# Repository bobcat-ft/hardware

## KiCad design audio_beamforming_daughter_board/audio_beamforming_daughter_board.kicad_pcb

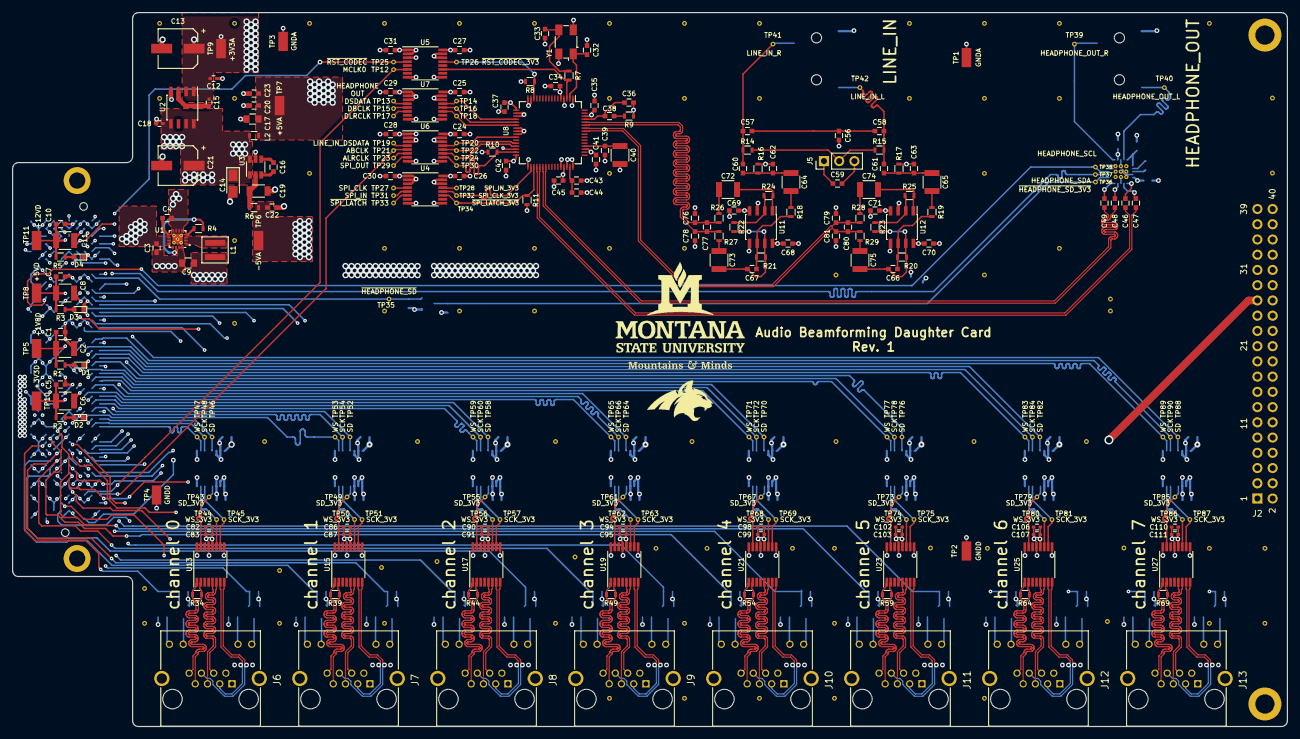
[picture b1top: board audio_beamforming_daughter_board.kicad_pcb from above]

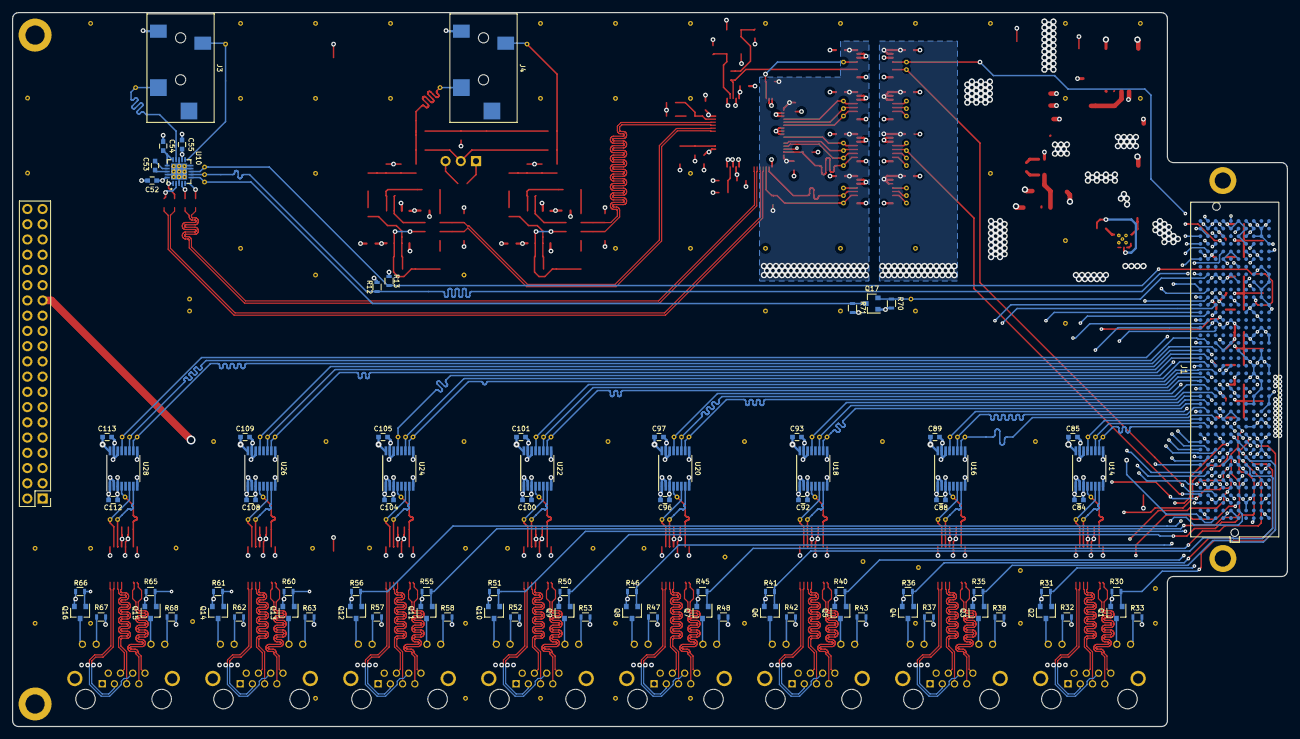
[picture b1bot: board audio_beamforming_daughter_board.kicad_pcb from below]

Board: 6 copper layers, 212.5 x 119.0 mm, 412 parts (86 on the bottom side), 266 nets.

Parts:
C1, C5, C7, C10, C22, C44: 10uF; C_0603
C2, C6, C8, C11: 100uF; C_1210
C3, C20: 10nF; C_0603
C4: 3300pF; C_0603
C9, C17: 22uF; C_0805
C12, C18, C82, C86, C90, C94, C98, C102, C106, C110: 0.1uF; C_0402
C13, C21: 47uF; CP_Elec_6.3x5.8
C14: 10uF; CP_Tantalum_Case-A_EIA-3216-18_Reflow
C15: 10nF; C_0402
C16, C23, C24, C25, C26, C27, C28, C29, C30, C31, C34, C35, C37, C39, C41, C42, C43, C45, C59, C68, C69, C70, C71, C84, C85, C88, C89, C92, C93, C96, C97, C100, C101, C104, C105, C108, C109, C112, C113: 0.1uF; C_0603
C19: 22uF; C_1206
C32, C33: 22pF; C_0603
C36: 390pF; C_0603
C38: 5600pF; C_0603
C40, C64, C65, C72, C73, C74, C75: 47uF; C_1210
C46, C47, C48, C49: 0.47uF; C_0603
C52, C53, C54, C55, C60, C61: 1.0uF; C_0603
C56, C57, C58, C76, C78, C79, C81: 1000pF; C_0603
C62, C63, C77, C80: 100pF; C_0603
C66, C67: 120pF; C_0603
C83, C87, C91, C95, C99, C103, C107, C111: 4700pF; C_0402
D1, D2, D3, D4: SML-LX0603SRW-TR; LED_0603
J1: ASP-134488-01; asp-134488-01
J2: TSW-120-07-F-D; Pin_Header_Straight_2x20_Pitch2.54mm
J3, J4: SJ-3523-SMT-TR; sj-352x-smt
J5: TSW-103-07-G-S; Pin_Header_Straight_1x03_Pitch2.54mm
J6, J7, J8, J9, J10, J11, J12, J13: 615008137421; WURTH_615008137421
L1: 2.2uH; xfl4020
L2: BLM18BA220SN1D; L_0603
Q1, Q2, Q3, Q4, Q5, Q6, Q7, Q8, Q9, Q10, Q11, Q12, Q13, Q14, Q15, Q16, Q17: NX138AKR; SOT-23
R1: 6.2; R_0603
R2: 107; R_0603
R3: 220; R_0603
R4: 100k; R_0603
R5: 680; R_0603
R6: 3.9; R_0603
R7: 49.9; R_0603
R8, R10, R11, R12, R13, R30, R31, R35, R36, R40, R41, R45, R46, R50, R51, R55, R56, R60, R61, R65, R66, R70, R71: 10k; R_0603
R9: 562; R_0603
R14, R15: 6.81k; R_0603
R16, R17: 4.99k; R_0603
R18, R19, R20, R21, R22, R23, R24, R25: 5.76k; R_0603
R26, R27, R28, R29: 237; R_0603
R32, R33, R37, R38, R42, R43, R47, R48, R52, R53, R57, R58, R62, R63, R67, R68: 330; R_0603
R34, R39, R44, R49, R54, R59, R64, R69: 100; R_0603
TP1, TP3: GNDA; Measurement_Point_SMD_1206
TP2, TP4: GNDD; Measurement_Point_SMD_1206
TP5: +1V8D; Measurement_Point_SMD_1206
TP6: -5VA; Measurement_Point_SMD_1206
TP7: +5VA; Measurement_Point_SMD_1206
TP8: +5VD; Measurement_Point_SMD_1206
TP9: +3V3A; Measurement_Point_SMD_1206
TP10: +3V3D; Measurement_Point_SMD_1206
TP11: +12VD; Measurement_Point_SMD_1206
TP12: MCLK0; Measurement_Point_Round-TH_0.4mm
TP13: HEADPHONE_OUT_DSDATA; Measurement_Point_Round-TH_0.4mm
TP14: HEADPHONE_OUT_DSDATA_3V3; Measurement_Point_Round-TH_0.4mm
TP15: DBCLK; Measurement_Point_Round-TH_0.4mm
TP16: DBCLK_3V3; Measurement_Point_Round-TH_0.4mm
TP17: DLRCLK; Measurement_Point_Round-TH_0.4mm
TP18: DLRCLK_3V3; Measurement_Point_Round-TH_0.4mm
TP19: LINE_IN_DSDATA; Measurement_Point_Round-TH_0.4mm
TP20: LINE_IN_DSDATA_3V3; Measurement_Point_Round-TH_0.4mm
TP21: ABCLK; Measurement_Point_Round-TH_0.4mm
TP22: ABCLK_3V3; Measurement_Point_Round-TH_0.4mm
TP23: ALRCLK; Measurement_Point_Round-TH_0.4mm
TP24: ALRCLK_3V3; Measurement_Point_Round-TH_0.4mm
TP25: ~RST_CODEC; Measurement_Point_Round-TH_0.4mm
TP26: ~RST_CODEC_3V3; Measurement_Point_Round-TH_0.4mm
TP27: SPI_IN; Measurement_Point_Round-TH_0.4mm
TP28: SPI_IN_3V3; Measurement_Point_Round-TH_0.4mm
TP29: SPI_OUT; Measurement_Point_Round-TH_0.4mm
TP30: SPI_OUT_3V3; Measurement_Point_Round-TH_0.4mm
TP31: SPI_CLK; Measurement_Point_Round-TH_0.4mm
TP32: SPI_CLK_3V3; Measurement_Point_Round-TH_0.4mm
TP33: ~SPI_LATCH; Measurement_Point_Round-TH_0.4mm
TP34: ~SPI_LATCH_3V3; Measurement_Point_Round-TH_0.4mm
TP35: ~HEADPHONE_SD; Measurement_Point_Round-TH_0.4mm
TP36: ~HEADPHONE_SD_3V3; Measurement_Point_Round-TH_0.4mm
TP37: HEADPHONE_SDA; Measurement_Point_Round-TH_0.4mm
TP38: HEADPHONE_SCL; Measurement_Point_Round-TH_0.4mm
TP39: HEADPHONE_OUT_R; Measurement_Point_Round-TH_0.4mm
TP40: HEADPHONE_OUT_L; Measurement_Point_Round-TH_0.4mm
TP41: LINE_IN_R; Measurement_Point_Round-TH_0.4mm
TP42: LINE_IN_L; Measurement_Point_Round-TH_0.4mm
TP43, TP49, TP55, TP61, TP67, TP73, TP79, TP85: SD_3V3; Measurement_Point_Round-TH_0.4mm
TP44, TP50, TP56, TP62, TP68, TP74, TP80, TP86: WS_3V3; Measurement_Point_Round-TH_0.4mm
TP45, TP51, TP57, TP63, TP69, TP75, TP81, TP87: SCK_3V3; Measurement_Point_Round-TH_0.4mm
TP46, TP52, TP58, TP64, TP70, TP76, TP82, TP88: SD; Measurement_Point_Round-TH_0.4mm
TP47, TP53, TP59, TP65, TP71, TP77, TP83, TP89: WS; Measurement_Point_Round-TH_0.4mm
TP48, TP54, TP60, TP66, TP72, TP78, TP84, TP90: SCK; Measurement_Point_Round-TH_0.4mm
U1: TPS62153RGTT; ti_vqfn-16
U2: ADP3303ARZ-3.3-RL7; SOIC-8_3.9x4.9mm_Pitch1.27mm
U3: LTC1983ES6-5#TRMPBF; TSOT-23-6
U4, U5, U6, U7, U14, U16, U18, U20, U22, U24, U26, U28: 74AVC4T245; TSSOP-16_4.4x5mm_Pitch0.65mm
U8: AD1939YSTZ; LQFP-64_10x10mm_Pitch0.5mm
U10: TPA6130A2; ti_pwqfn_n20
U11, U12: ADA4075-2; SOIC-8_3.9x4.9mm_Pitch1.27mm
U13, U15, U17, U19, U21, U23, U25, U27: SN65LVDS049; TSSOP-16_4.4x5mm_Pitch0.65mm
V3_1, V3_2, V4_1, V4_2, V4_4, V4_5, V4_5#2, V4_5#3, V4_5#4, V4_5#5, V4_5#6, V4_5#7, V4_5#8, V4_5#9, V4_5#10, V4_5#11, V4_5#12, V4_5#13, V4_5#14, V4_5#15, V5_1, V5_3, V6_1, V6_4, V6_9, V6_9#2, V6_9#3, V6_9#4, V7_1, V7_4, V8_1, V8_4, V9_1, V9_2, V9_3, V9_4, V9_10, V10_1, V10_2, V10_4, V10_9, V10_9#2, V10_10, V11_1, V11_2, V11_10, V12_8, V12_8#2, V12_8#3, V12_8#4, V12_8#5, V12_8#6, V12_8#7, V12_8#8, V12_9, V12_10, V13_1, V13_2, V14_1, V14_2, V14_3, V14_8, V14_10, V15_1, V15_2, V15_4, V16_8, V16_8#2, V16_8#3, V17_1, V17_8, V17_8#2, V17_9, V17_9#2, V18_2, V18_3: AUTO_VIA; VIA_MATRIX
Y1: ABM3B-12.288MHZ-10-1-U-T; Crystal_SMD_Abracon_ABM3B-4pin_5.0x3.2mm

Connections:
+1V8D: C1.1, C2.1, C28.2, C29.2, C30.2, C31.2, C85.2, C89.2, C93.2, C97.2, C101.2, C105.2, C109.2, C113.2, J1.E39, J1.F40, J1.G39, J1.H01, J1.H40, J1.J39, J1.K01, J1.K40, J2.27, Q17.1, R1.2, R70.1, TP5.1, U4.1, U4.2, U4.3, U5.1, U5.2, U6.1, U7.1, U7.2, U7.3, U14.16, U16.16, U18.16, U20.16, U22.16, U24.16, U26.16, U28.16
+3V3A: C12.1, C13.1, C15.2, C34.2, C35.2, C36.2, C41.2, C45.1, R9.1, TP9.1, U2.1, U2.2, U8.5, U8.45, U8.51, U8.62
+3V3D: C5.1, C6.1, C24.2, C25.2, C26.2, C27.2, C37.1, C42.1, C82.2, C83.2, C84.2, C86.2, C87.2, C88.2, C90.2, C91.2, C92.2, C94.2, C95.2, C96.2, C98.2, C99.2, C100.2, C102.2, C103.2, C104.2, C106.2, C107.2, C108.2, C110.2, C111.2, C112.2, J1.C39, J1.D32, J1.D36, J1.D38, J1.D40, J2.31, J6.1, J7.1, J8.1, J9.1, J10.1, J11.1, J12.1, J13.1, R2.2, R8.2, R11.2, R12.1, R13.2, R32.1, R33.1, R37.1, R38.1, R42.1, R43.1, R47.1, R48.1, R52.1, R53.1, R57.1, R58.1, R62.1, R63.1, R67.1, R68.1, R71.1, TP10.1, U4.16, U5.16, U6.16, U7.16, U8.17, U8.32, U13.12, U13.16, U14.1, U14.2, U15.12, U15.16, U16.1, U16.2, U17.12, U17.16, U18.1, U18.2, U19.12, U19.16, U20.1, U20.2, U21.12, U21.16, U22.1, U22.2, U23.12, U23.16, U24.1, U24.2, U25.12, U25.16, U26.1, U26.2, U27.12, U27.16, U28.1, U28.2
+5VA: C17.1, C20.1, C23.1, C52.2, C55.2, C59.2, C68.2, C70.1, J5.3, L2.2, TP7.1, U10.12, U10.20, U11.8, U12.8
+5VD: C7.1, C8.1, C9.1, C14.1, C18.1, C21.1, J2.35, L1.2, L2.1, R3.2, R4.1, TP8.1, U1.14, U2.5, U2.7, U2.8, U3.1, U3.6
+12VD: C3.1, C10.1, C11.1, J1.C35, J1.C37, J2.39, R5.2, TP11.1, U1.10, U1.11, U1.12, U1.13
-5VA: C22.1, C69.1, C71.1, R6.1, TP6.1, U11.4, U12.4
/FMC Connector/ABCLK: J1.K04, TP21.1, U6.5
/FMC Connector/ALRCLK: J1.J37, TP23.1, U6.6
/FMC Connector/DBCLK: J1.H38, TP15.1, U7.5
/FMC Connector/DLRCLK: J1.K38, TP17.1, U7.6
/FMC Connector/GPIO0: J1.G10, J2.1
/FMC Connector/GPIO1: J1.F10, J2.2
/FMC Connector/GPIO2: J1.F11, J2.3
/FMC Connector/GPIO3: J1.G06, J2.4
/FMC Connector/GPIO4: J1.F07, J2.5
/FMC Connector/GPIO5: J1.G07, J2.6
/FMC Connector/GPIO6: J1.F08, J2.7
/FMC Connector/GPIO7: J1.J07, J2.8
/FMC Connector/GPIO8: J1.K07, J2.9
/FMC Connector/GPIO9: J1.H07, J2.10
/FMC Connector/GPIO10: J1.K08, J2.11
/FMC Connector/GPIO11: J1.H08, J2.12
/FMC Connector/GPIO12: J1.G09, J2.13
/FMC Connector/GPIO13: J1.J09, J2.14
/FMC Connector/GPIO14: J1.H10, J2.15
/FMC Connector/GPIO15: J1.K10, J2.16
/FMC Connector/GPIO16: J1.J10, J2.17
/FMC Connector/GPIO17: J1.K11, J2.18
/FMC Connector/GPIO18: J1.H26, J2.19
/FMC Connector/GPIO19: J1.K26, J2.20
/FMC Connector/GPIO20: J1.G27, J2.21
/FMC Connector/GPIO21: J1.J27, J2.22
/FMC Connector/GPIO22: J1.H28, J2.23
/FMC Connector/GPIO23: J1.J28, J2.24
/FMC Connector/GPIO24: J1.K28, J2.25
/FMC Connector/GPIO25: J1.H29, J2.26
/FMC Connector/GPIO26: J1.K29, J2.29
/FMC Connector/GPIO27: J1.G30, J2.30
/FMC Connector/GPIO28: J1.J30, J2.33
/FMC Connector/GPIO29: J1.H31, J2.34
/FMC Connector/GPIO30: J1.J31, J2.37
/FMC Connector/GPIO31: J1.K31, J2.38
/FMC Connector/HEADPHONE_OUT_DSDATA: J1.G37, TP13.1, U7.4
/FMC Connector/HEADPHONE_SCL: J1.C30, R13.1, TP38.1, U10.8
/FMC Connector/HEADPHONE_SDA: J1.C31, R12.2, TP37.1, U10.7
/FMC Connector/LINE_IN_DSDATA: J1.K37, TP19.1, U6.4
/FMC Connector/MCLK0: J1.H04, TP12.1, U5.6
/FMC Connector/SPI_CLK: J1.G36, TP31.1, U4.5
/FMC Connector/SPI_IN: J1.H37, TP27.1, U4.4
/FMC Connector/SPI_OUT: J1.J36, TP29.1, U6.7
/FMC Connector/~HEADPHONE_SD: J1.J33, Q17.2, R70.2, TP35.1
/FMC Connector/~RST_CODEC: J1.E34, TP25.1, U5.4
/FMC Connector/~SPI_LATCH: J1.K35, TP33.1, U4.6
/LED_SD_CH0: J1.C10, Q2.1, R31.1
/LED_SD_CH1: J1.E10, Q4.1, R36.1
/LED_SD_CH2: J1.D08, Q6.1, R41.1
/LED_SD_CH3: J1.E06, Q8.1, R46.1
/LED_SD_CH4: J1.E12, Q10.1, R51.1
/LED_SD_CH5: J1.F13, Q12.1, R56.1
/LED_SD_CH6: J1.E03, Q14.1, R61.1
/LED_SD_CH7: J1.F05, Q16.1, R66.1
/LED_WS_CH0: J1.C11, Q1.1, R30.1
/LED_WS_CH1: J1.D09, Q3.1, R35.1
/LED_WS_CH2: J1.D11, Q5.1, R40.1
/LED_WS_CH3: J1.E09, Q7.1, R45.1
/LED_WS_CH4: J1.D12, Q9.1, R50.1
/LED_WS_CH5: J1.E13, Q11.1, R55.1
/LED_WS_CH6: J1.E02, Q13.1, R60.1
/LED_WS_CH7: J1.F04, Q15.1, R65.1
/Microphone Array Interface Ch0/SCK+: J6.3, U13.7
/Microphone Array Interface Ch0/SCK-: J6.6, U13.8
/Microphone Array Interface Ch0/SCK_3V3: TP45.1, U13.10, U14.6
/Microphone Array Interface Ch0/SD+: J6.7, R34.1, U13.2
/Microphone Array Interface Ch0/SD-: J6.8, R34.2, U13.1
/Microphone Array Interface Ch0/SD_3V3: TP43.1, U13.15, U14.4
/Microphone Array Interface Ch0/WS+: J6.4, U13.6
/Microphone Array Interface Ch0/WS-: J6.5, U13.5
/Microphone Array Interface Ch0/WS_3V3: TP44.1, U13.11, U14.7
/Microphone Array Interface Ch1/SCK+: J7.3, U15.7
/Microphone Array Interface Ch1/SCK-: J7.6, U15.8
/Microphone Array Interface Ch1/SCK_3V3: TP51.1, U15.10, U16.6
/Microphone Array Interface Ch1/SD+: J7.7, R39.1, U15.2
/Microphone Array Interface Ch1/SD-: J7.8, R39.2, U15.1
/Microphone Array Interface Ch1/SD_3V3: TP49.1, U15.15, U16.4
/Microphone Array Interface Ch1/WS+: J7.4, U15.6
/Microphone Array Interface Ch1/WS-: J7.5, U15.5
/Microphone Array Interface Ch1/WS_3V3: TP50.1, U15.11, U16.7
/Microphone Array Interface Ch2/SCK+: J8.3, U17.7
/Microphone Array Interface Ch2/SCK-: J8.6, U17.8
/Microphone Array Interface Ch2/SCK_3V3: TP57.1, U17.10, U18.6
/Microphone Array Interface Ch2/SD+: J8.7, R44.1, U17.2
/Microphone Array Interface Ch2/SD-: J8.8, R44.2, U17.1
/Microphone Array Interface Ch2/SD_3V3: TP55.1, U17.15, U18.4
/Microphone Array Interface Ch2/WS+: J8.4, U17.6
/Microphone Array Interface Ch2/WS-: J8.5, U17.5
/Microphone Array Interface Ch2/WS_3V3: TP56.1, U17.11, U18.7
/Microphone Array Interface Ch3/SCK+: J9.3, U19.7
/Microphone Array Interface Ch3/SCK-: J9.6, U19.8
/Microphone Array Interface Ch3/SCK_3V3: TP63.1, U19.10, U20.6
/Microphone Array Interface Ch3/SD+: J9.7, R49.1, U19.2
/Microphone Array Interface Ch3/SD-: J9.8, R49.2, U19.1
/Microphone Array Interface Ch3/SD_3V3: TP61.1, U19.15, U20.4
/Microphone Array Interface Ch3/WS+: J9.4, U19.6
/Microphone Array Interface Ch3/WS-: J9.5, U19.5
/Microphone Array Interface Ch3/WS_3V3: TP62.1, U19.11, U20.7
/Microphone Array Interface Ch4/SCK+: J10.3, U21.7
/Microphone Array Interface Ch4/SCK-: J10.6, U21.8
/Microphone Array Interface Ch4/SCK_3V3: TP69.1, U21.10, U22.6
/Microphone Array Interface Ch4/SD+: J10.7, R54.1, U21.2
/Microphone Array Interface Ch4/SD-: J10.8, R54.2, U21.1
/Microphone Array Interface Ch4/SD_3V3: TP67.1, U21.15, U22.4
/Microphone Array Interface Ch4/WS+: J10.4, U21.6
/Microphone Array Interface Ch4/WS-: J10.5, U21.5
/Microphone Array Interface Ch4/WS_3V3: TP68.1, U21.11, U22.7
/Microphone Array Interface Ch5/SCK+: J11.3, U23.7
/Microphone Array Interface Ch5/SCK-: J11.6, U23.8
/Microphone Array Interface Ch5/SCK_3V3: TP75.1, U23.10, U24.6
/Microphone Array Interface Ch5/SD+: J11.7, R59.1, U23.2
/Microphone Array Interface Ch5/SD-: J11.8, R59.2, U23.1
/Microphone Array Interface Ch5/SD_3V3: TP73.1, U23.15, U24.4
/Microphone Array Interface Ch5/WS+: J11.4, U23.6
/Microphone Array Interface Ch5/WS-: J11.5, U23.5
/Microphone Array Interface Ch5/WS_3V3: TP74.1, U23.11, U24.7
/Microphone Array Interface Ch6/SCK+: J12.3, U25.7
/Microphone Array Interface Ch6/SCK-: J12.6, U25.8
/Microphone Array Interface Ch6/SCK_3V3: TP81.1, U25.10, U26.6
/Microphone Array Interface Ch6/SD+: J12.7, R64.1, U25.2
/Microphone Array Interface Ch6/SD-: J12.8, R64.2, U25.1
/Microphone Array Interface Ch6/SD_3V3: TP79.1, U25.15, U26.4
/Microphone Array Interface Ch6/WS+: J12.4, U25.6
/Microphone Array Interface Ch6/WS-: J12.5, U25.5
/Microphone Array Interface Ch6/WS_3V3: TP80.1, U25.11, U26.7
/Microphone Array Interface Ch7/SCK+: J13.3, U27.7
/Microphone Array Interface Ch7/SCK-: J13.6, U27.8
/Microphone Array Interface Ch7/SCK_3V3: TP87.1, U27.10, U28.6
/Microphone Array Interface Ch7/SD+: J13.7, R69.1, U27.2
/Microphone Array Interface Ch7/SD-: J13.8, R69.2, U27.1
/Microphone Array Interface Ch7/SD_3V3: TP85.1, U27.15, U28.4
/Microphone Array Interface Ch7/WS+: J13.4, U27.6
/Microphone Array Interface Ch7/WS-: J13.5, U27.5
/Microphone Array Interface Ch7/WS_3V3: TP86.1, U27.11, U28.7
/SCK_CH0: J1.J13, TP48.1, U14.11
/SCK_CH1: J1.J15, TP54.1, U16.11
/SCK_CH2: J1.J16, TP60.1, U18.11
/SCK_CH3: J1.J18, TP66.1, U20.11
/SCK_CH4: J1.J19, TP72.1, U22.11
/SCK_CH5: J1.J21, TP78.1, U24.11
/SCK_CH6: J1.J22, TP84.1, U26.11
/SCK_CH7: J1.J24, TP90.1, U28.11
/SD_CH0: J1.K14, TP46.1, U14.13
/SD_CH1: J1.G15, TP52.1, U16.13
/SD_CH2: J1.K17, TP58.1, U18.13
/SD_CH3: J1.G18, TP64.1, U20.13
/SD_CH4: J1.K20, TP70.1, U22.13
/SD_CH5: J1.G21, TP76.1, U24.13
/SD_CH6: J1.K23, TP82.1, U26.13
/SD_CH7: J1.G24, TP88.1, U28.13
/WS_CH0: J1.K13, TP47.1, U14.10
/WS_CH1: J1.H14, TP53.1, U16.10
/WS_CH2: J1.K16, TP59.1, U18.10
/WS_CH3: J1.H17, TP65.1, U20.10
/WS_CH4: J1.K19, TP71.1, U22.10
/WS_CH5: J1.H20, TP77.1, U24.10
/WS_CH6: J1.K22, TP83.1, U26.10
/WS_CH7: J1.H23, TP89.1, U28.10
/audio_codec/ABCLK_3V3: TP22.1, U6.12, U8.28
/audio_codec/ALRCLK_3V3: TP24.1, U6.11, U8.29
/audio_codec/DBCLK_3V3: TP16.1, U7.12, U8.21
/audio_codec/DLRCLK_3V3: TP18.1, U7.11, U8.22
/audio_codec/HEADPHONE_OUT_DSDATA_3V3: TP14.1, U7.13, U8.20
/audio_codec/HEADPHONE_OUT_L_N: C46.2, U8.37
/audio_codec/HEADPHONE_OUT_L_P: C47.2, U8.36
/audio_codec/HEADPHONE_OUT_R_N: C49.2, U8.39
/audio_codec/HEADPHONE_OUT_R_P: C48.2, U8.38
/audio_codec/LINE_IN_DSDATA_3V3: TP20.1, U6.13, U8.26
/audio_codec/LINE_IN_L_N: C79.1, C80.2, R28.2, U8.58
/audio_codec/LINE_IN_L_P: C80.1, C81.2, R29.2, U8.57
/audio_codec/LINE_IN_R_N: C76.1, C77.2, R26.2, U8.60
/audio_codec/LINE_IN_R_P: C77.1, C78.2, R27.2, U8.59
/audio_codec/MCLK0_3V3: R7.1, U5.11, U8.3
/audio_codec/MCLKI: C32.1, U8.2, Y1.1
/audio_codec/SPI_CLK_3V3: TP32.1, U4.12, U8.34
/audio_codec/SPI_IN_3V3: TP28.1, U4.13, U8.30
/audio_codec/SPI_OUT_3V3: R10.1, TP30.1, U6.10, U8.31
/audio_codec/~RST_CODEC_3V3: R8.1, TP26.1, U5.13, U8.14
/audio_codec/~SPI_LATCH_3V3: R11.1, TP34.1, U4.11, U8.35
/headphone_out/HEADPHONE_OUT_L: J3.1, TP40.1, U10.14
/headphone_out/HEADPHONE_OUT_R: J3.2, TP39.1, U10.11
/headphone_out/~HEADPHONE_SD_3V3: Q17.3, R71.2, TP36.1, U10.6
/line_in/LINE_IN_L: C58.2, C61.2, J4.1, R15.2, TP42.1
/line_in/LINE_IN_R: C57.1, C60.2, J4.2, R14.1, TP41.1
GND: C1.2, C2.2, C3.2, C4.2, C5.2, C6.2, C7.2, C8.2, C9.2, C10.2, C11.2, C12.2, C13.2, C14.2, C17.2, C18.2, C19.2, C20.2, C21.2, C22.2, C23.2, C24.1, C25.1, C26.1, C27.1, C28.1, C29.1, C30.1, C31.1, C32.2, C33.2, C34.1, C35.1, C37.2, C39.1, C40.1, C41.1, C42.2, C43.1, C44.1, C45.2, C52.1, C54.1, C55.1, C56.2, C59.1, C62.1, C63.1, C68.1, C69.2, C70.2, C71.2, C76.2, C78.1, C79.2, C81.1, C82.1, C83.1, C84.1, C85.1, C86.1, C87.1, C88.1, C89.1, C90.1, C91.1, C92.1, C93.1, C94.1, C95.1, C96.1, C97.1, C98.1, C99.1, C100.1, C101.1, C102.1, C103.1, C104.1, C105.1, C106.1, C107.1, C108.1, C109.1, C110.1, C111.1, C112.1, C113.1, D1.1, D2.1, D3.1, D4.1, J1.A01, J1.A04, J1.A05, J1.A08, J1.A09, J1.A12, J1.A13, J1.A16, J1.A17, J1.A20, J1.A21, J1.A24, J1.A25, J1.A28, J1.A29, J1.A32, J1.A33, J1.A36, J1.A37, J1.A40, J1.B02, J1.B03, J1.B06, J1.B07, J1.B10, J1.B11, J1.B14, J1.B15, J1.B18, J1.B19, J1.B22, J1.B23, J1.B26, J1.B27, J1.B30, J1.B31, J1.B34, J1.B35, J1.B38, J1.B39, J1.C01, J1.C04, J1.C05, J1.C08, J1.C09, J1.C12, J1.C13, J1.C16, J1.C17, J1.C20, J1.C21, J1.C24, J1.C25, J1.C28, J1.C29, J1.C32, J1.C33, J1.C36, J1.C38, J1.C40, J1.D02, J1.D03, J1.D06, J1.D07, J1.D10, J1.D13, J1.D16, J1.D19, J1.D22, J1.D25, J1.D28, J1.D37, J1.D39, J1.E01, J1.E04, J1.E05, J1.E08, J1.E11, J1.E14, J1.E17, J1.E20, J1.E23, J1.E26, J1.E29, J1.E32, J1.E35, J1.E38, J1.E40, J1.F02, J1.F03, J1.F06, J1.F09, J1.F12, J1.F15, J1.F18, J1.F21, J1.F24, J1.F27, J1.F30, J1.F33, J1.F36, J1.F39, J1.G01, J1.G04, J1.G05, J1.G08, J1.G11, J1.G14, J1.G17, J1.G20, J1.G23, J1.G26, J1.G29, J1.G32, J1.G35, J1.G38, J1.G40, J1.H03, J1.H06, J1.H09, J1.H12, J1.H15, J1.H18, J1.H21, J1.H24, J1.H27, J1.H30, J1.H33, J1.H36, J1.H39, J1.J01, J1.J04, J1.J05, J1.J08, J1.J11, J1.J14, J1.J17, J1.J20, J1.J23, J1.J26, J1.J29, J1.J32, J1.J35, J1.J38, J1.J40, J1.K02, J1.K03, J1.K06, J1.K09, J1.K12, J1.K15, J1.K18, J1.K21, J1.K24, J1.K27, J1.K30, J1.K33, J1.K36, J1.K39, J2.28, J2.32, J2.36, J2.40, J3.3, J4.3, J5.1, J6.2, J6.13, J6.14, J7.2, J7.13, J7.14, J8.2, J8.13, J8.14, J9.2, J9.13, J9.14, J10.2, J10.13, J10.14, J11.2, J11.13, J11.14, J12.2, J12.13, J12.14, J13.2, J13.13, J13.14, Q1.2, Q2.2, Q3.2, Q4.2, Q5.2, Q6.2, Q7.2, Q8.2, Q9.2, Q10.2, Q11.2, Q12.2, Q13.2, Q14.2, Q15.2, Q16.2, R10.2, R16.1, R17.1, R30.2, R31.2, R35.2, R36.2, R40.2, R41.2, R45.2, R46.2, R50.2, R51.2, R55.2, R56.2, R60.2, R61.2, R65.2, R66.2, TP1.1, TP2.1, TP3.1, TP4.1, U1.5, U1.6, U1.7, U1.8, U1.15, U1.16, U1.17, U2.4, U3.5, U4.8, U4.9, U4.14, U4.15, U5.3, U5.8, U5.9, U5.14, U5.15, U6.2, U6.3, U6.8, U6.9, U6.14, U6.15, U7.8, U7.9, U7.14, U7.15, U8.1, U8.4, U8.15, U8.16, U8.18, U8.19, U8.23, U8.24, U8.25, U8.33, U8.44, U8.46, U8.48, U10.3, U10.9, U10.10, U10.13, U10.19, U10.21, U11.3, U11.5, U12.3, U12.5, U13.9, U13.13, U14.3, U14.8, U14.9, U14.14, U14.15, U15.9, U15.13, U16.3, U16.8, U16.9, U16.14, U16.15, U17.9, U17.13, U18.3, U18.8, U18.9, U18.14, U18.15, U19.9, U19.13, U20.3, U20.8, U20.9, U20.14, U20.15, U21.9, U21.13, U22.3, U22.8, U22.9, U22.14, U22.15, U23.9, U23.13, U24.3, U24.8, U24.9, U24.14, U24.15, U25.9, U25.13, U26.3, U26.8, U26.9, U26.14, U26.15, U27.9, U27.13, U28.3, U28.8, U28.9, U28.14, U28.15, V3_1.1, V3_2.1, V4_1.1, V4_2.1, V4_4.1, V4_5.1, V4_5#2.1, V4_5#3.1, V4_5#4.1, V4_5#5.1, V4_5#6.1, V4_5#7.1, V4_5#8.1, V4_5#9.1, V4_5#10.1, V4_5#11.1, V4_5#12.1, V4_5#13.1, V4_5#14.1, V4_5#15.1, V5_1.1, V5_3.1, V6_1.1, V6_4.1, V6_9.1, V6_9#2.1, V6_9#3.1, V6_9#4.1, V7_1.1, V7_4.1, V8_1.1, V8_4.1, V9_1.1, V9_2.1, V9_3.1, V9_4.1, V9_10.1, V10_1.1, V10_2.1, V10_4.1, V10_9.1, V10_9#2.1, V10_10.1, V11_1.1, V11_2.1, V11_10.1, V12_8.1, V12_8#2.1, V12_8#3.1, V12_8#4.1, V12_8#5.1, V12_8#6.1, V12_8#7.1, V12_8#8.1, V12_9.1, V12_10.1, V13_1.1, V13_2.1, V14_1.1, V14_2.1, V14_3.1, V14_8.1, V14_10.1, V15_1.1, V15_2.1, V15_4.1, V16_8.1, V16_8#2.1, V16_8#3.1, V17_1.1, V17_8.1, V17_8#2.1, V17_9.1, V17_9#2.1, V18_2.1, V18_3.1, Y1.2, Y1.4
unnamed: C4.1, U1.9
unnamed: C15.1, U2.3
unnamed: C16.1, U3.4
unnamed: C16.2, U3.3
unnamed: C19.1, R6.2, U3.2
unnamed: C33.1, R7.2, Y1.3
unnamed: C36.1, C38.1, U8.61
unnamed: C38.2, R9.2
unnamed: C39.2, C40.2, U8.52
unnamed: C43.2, C44.2, U8.47
unnamed: C46.1, U10.1
unnamed: C47.1, U10.2
unnamed: C48.1, U10.4
unnamed: C49.1, U10.5
unnamed: C53.1, U10.17
unnamed: C53.2, U10.18
unnamed: C54.2, U10.15, U10.16
unnamed: C56.1, C57.2, C58.1
unnamed: C60.1, C62.2, C64.1, R16.2
unnamed: C61.1, C63.2, C65.1, R17.2
unnamed: C64.2, R18.1
unnamed: C65.2, R19.1
unnamed: C66.1, R19.2, R20.1, U12.6
unnamed: C66.2, C75.2, R20.2, R23.1, U12.7
unnamed: C67.1, R18.2, R21.1, U11.6
unnamed: C67.2, C73.2, R21.2, R22.1, U11.7
unnamed: C72.1, R26.1
unnamed: C72.2, R24.2, U11.1
unnamed: C73.1, R27.1
unnamed: C74.1, R28.1
unnamed: C74.2, R25.2, U12.1
unnamed: C75.1, R29.1
unnamed: D1.2, R1.1
unnamed: D2.2, R2.1
unnamed: D3.2, R3.1
unnamed: D4.2, R5.1
unnamed: J5.2, R14.2, R15.1
unnamed: J6.9, R33.2
unnamed: J6.10, Q1.3
unnamed: J6.11, R32.2
unnamed: J6.12, Q2.3
unnamed: J7.9, R38.2
unnamed: J7.10, Q3.3
unnamed: J7.11, R37.2
unnamed: J7.12, Q4.3
unnamed: J8.9, R43.2
unnamed: J8.10, Q5.3
unnamed: J8.11, R42.2
unnamed: J8.12, Q6.3
unnamed: J9.9, R48.2
unnamed: J9.10, Q7.3
unnamed: J9.11, R47.2
unnamed: J9.12, Q8.3
unnamed: J10.9, R53.2
unnamed: J10.10, Q9.3
unnamed: J10.11, R52.2
unnamed: J10.12, Q10.3
unnamed: J11.9, R58.2
unnamed: J11.10, Q11.3
unnamed: J11.11, R57.2
unnamed: J11.12, Q12.3
unnamed: J12.9, R63.2
unnamed: J12.10, Q13.3
unnamed: J12.11, R62.2
unnamed: J12.12, Q14.3
unnamed: J13.9, R68.2
unnamed: J13.10, Q15.3
unnamed: J13.11, R67.2
unnamed: J13.12, Q16.3
unnamed: L1.1, U1.1, U1.2, U1.3
unnamed: R4.2, U1.4
unnamed: R22.2, R24.1, U11.2
unnamed: R23.2, R25.1, U12.2

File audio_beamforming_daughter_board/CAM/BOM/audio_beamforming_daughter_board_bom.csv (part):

Description,Part,References,Value,Footprint,Quantity Per PCB,Datasheet,Vendor,Manufacturer Part Number,Config,Vendor Part Number,Manufacturer
CAP CER 0.1UF 25V X7R 0603,C_Small,C16 C23 C24 C25 C26 C27 C28 C29 C30 C31 C34 C35 C37 C39 C41 C42 C43 C45 C68 C69 C70 C71 C84 C85 C88 C89 C92 C93 C96 C97 C100 C101 C104 C105 C108 C109 C112 C113,0.1uF,C_0603,38,https://product.tdk.com/info/en/catalog/datasheets/mlcc_auto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,Digi-Key,CGA3E2X7R1E104K080AA,load,445-5667-1-ND,TDK Corporation
CAP CER 0.1UF 50V 10% X7R 0402,C_Small,C12 C18 C82 C86 C90 C94 C98 C102 C106 C110,0.1uF,C_0402,10,https://product.tdk.com/info/en/catalog/datasheets/mlcc_comm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,Digi-Key,CGA2B1X7R1C104M050BC,load,445-12242-1-ND,TDK Corporation
CAP CER 0.47UF 16V X7R 0603,C_Small,C46 C47 C48 C49,0.47uF,C_0603,4,https://product.tdk.com/info/en/catalog/datasheets/mlcc_auto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,Digi-Key,CGA3E1X7R1C474M080AC,load,445-12537-1-ND,TDK Corporation
CAP CER 1UF 16V X7R 0603,C_Small,C52 C53 C54 C55 C60 C61,1.0uF,C_0603,6,https://product.tdk.com/info/en/catalog/datasheets/mlcc_auto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,Digi-Key,CGA3E1X7R1C105M080AC,load,445-12540-1-ND,TDK Corporation
"1000pF 50V Ceramic Capacitor X7R 0603 (1608 Metric) 0.063"" L x 0.031"" W (1.60mm x 0.80mm)",C_Small,C76 C78 C79 C81,1000pF,C_0603,4,https://media.digikey.com/pdf/Data%20Sheets/Samsung%20PDFs/C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,Digi-Key,CL10B102KB8NNNC,load,1276-1018-1-ND,"Samsung Electro-Mechanics America, Inc."
CAP CER 100PF 100V 5% NP0 0603,C_Small,C62 C63 C77 C80,100pF,C_0603,4,https://product.tdk.com/info/en/catalog/datasheets/mlcc_comm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,Digi-Key,C1608C0G2A101J,load,445-2306-1-ND,TDK Corporation
"100µF 6.3V Ceramic Capacitor X6S 1210 (3225 Metric) 0.126"" L x 0.098"" W (3.20mm x 2.50mm)",C_Small,C2 C6 C8 C11,100uF,C_1210,4,http://www.samsungsem.com/kr/support/product-search/mlcc/CL3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,Digi-Key,CL32X107MQVNNNE,load,1276-3399-1-ND,"Samsung Electro-Mechanics America, Inc."
CAP CER 10000PF 100V X7R 0603,C_Small,C15,10nF,C_0402,1,https://product.tdk.com/info/en/catalog/datasheets/mlcc_comm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,Digi-Key,C1608X7R2A103K080AA,load,445-1304-1-ND,TDK Corporation
CAP CER 10000PF 50V 5% X7R 0603,C_Small,C3 C20,10nF,C_0603,2,https://search.kemet.com/component-edge/download/datasheet/C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,Digi-Key,C0603C103J5RACTU,load,399-1092-1-ND,Kemet
CAP CER 10UF 10V 10% X5R 0603,C_Small,C1 C5 C7 C10 C22 C44,10uF,C_0603,6,https://product.tdk.com/info/en/catalog/datasheets/mlcc_comm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,Digi-Key,C1608X5R1A106K,load,445-7486-1-ND,TDK Corporation
CAP TANT 10UF 10V 10% 1206,CP1_Small,C14,10uF,CP_Tantalum_Case-A_EIA-3216-18_Reflow,1,http://datasheets.avx.com/TPS.pdf,Digi-Key,TPSA106K010R0900,load,478-1751-1-ND,AVX Corporation
"120pF 50V Ceramic Capacitor C0G, NP0 0603 (1608 Metric) 0.063"" L x 0.031"" W (1.60mm x 0.80mm)",C_Small,C66 C67,120pF,C_0603,2,https://media.digikey.com/pdf/Data%20Sheets/Samsung%20PDFs/C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,Digi-Key,CL10C121JB8NCNC,load,1276-2180-1-ND,"Samsung Electro-Mechanics America, Inc."
CAP CER 22PF 50V C0G 0603,C_Small,C32 C33,22pF,C_0603,2,https://product.tdk.com/info/en/catalog/datasheets/mlcc_auto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,Digi-Key,CGA3E2C0G1H220J080AA,load,445-5632-1-ND,TDK Corporation
CAP CER 22UF 10V X5R 0805,C_Small,C9 C17,22uF,C_0805,2,http://www.samsungsem.com/kr/support/product-search/mlcc/CL2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,Digi-Key,CL21A226KPCLRNC,load,1276-6786-1-ND,"Samsung Electro-Mechanics America, Inc."
CAP CER 22UF 16V 20% X6S 1206,C_Small,C19,22uF,C_1206,1,https://product.tdk.com/info/en/catalog/datasheets/mlcc_comm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,Digi-Key,C3216X6S1C226M,load,445-8044-1-ND,TDK Corporation
CAP CER 3300PF 50V X7R 0603,C_Small,C4,3300pF,C_0603,1,https://product.tdk.com/info/en/catalog/datasheets/mlcc_auto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,Digi-Key,CGA3E2X7R1H332K080AA,load,445-6921-1-ND,TDK Corporation
"390pF 50V Ceramic Capacitor X7R 0603 (1608 Metric) 0.063"" L x 0.031"" W (1.60mm x 0.80mm)",C_Small,C36,390pF,C_0603,1,https://media.digikey.com/pdf/Data%20Sheets/Samsung%20PDFs/C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,Digi-Key,CL10B391KB8NNNC,load,1276-2049-1-ND,"Samsung Electro-Mechanics America, Inc."
CGA2B2X7R1H472M050BA,C_Small,C83 C87 C91 C95 C99 C103 C107 C111,4700pF,C_0402,8,https://product.tdk.com/info/en/catalog/datasheets/mlcc_auto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,Digi-Key,CGA2B2X7R1H472M050BA,load,445-12278-1-ND,TDK Corporation
CAP ALUM 47UF 50V 20% SMD,CP1_Small,C13 C21,47uF,CP_Elec_6.3x5.8,2,https://industrial.panasonic.com/cdbs/www-data/pdf/RDE0000/A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,Digi-Key,EEE-FT1H470AP,load,PCE5023CT-ND,Panasonic - ECG
47µF ±10% 16V Ceramic Capacitor X6S 1210 (3225 Metric),C_Small,C40 C64 C65 C72 C73 C74 C75,47uF,C_1210,7,http://search.murata.co.jp/Ceramy/image/img/A01X/G101/ENG/GR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,Digi-Key,GRM32EC81C476KE15L,load,490-10531-1-ND,Murata Electronics North America
"5600pF 50V Ceramic Capacitor X7R 0603 (1608 Metric) 0.063"" L x 0.031"" W (1.60mm x 0.80mm)",C_Small,C38,5600pF,C_0603,1,https://media.digikey.com/pdf/Data%20Sheets/Samsung%20PDFs/C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,Digi-Key,CL10B562KB8SFNC,load,1276-2092-1-ND,"Samsung Electro-Mechanics America, Inc."
LED RED DIFFUSED 0603 SMD,LED,D1 D2 D3 D4,SML-LX0603SRW-TR,LED_0603,4,http://www.lumex.com/content/files/ProductAttachment/SML-LX0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,Digi-Key,SML-LX0603SRW-TR,load,67-1551-1-ND,Lumex Opto/Components Inc.
CONN MOD JACK 8P8C R/A SHIELDED,615008137421,J6 J7 J8 J9 J10 J11 J12 J13,615008137421,WURTH_615008137421,8,http://katalog.we-online.de/em/datasheet/615008137421.pdf,Digi-Key,615008137421,load,732-2112-ND,Wurth Electronics Inc.
CONN SNGL-END ARRAY MALE 400POS,ASP-134488-01,J1,ASP-134488-01,asp-134488-01,1,http://suddendocs.samtec.com/prints/asp-134488-01.pdf,Digi-Key,ASP-134488-01,load,SAM8730-ND,Samtec Inc.
"3.50mm (0.141"", 1/8"", Mini Plug) - Headphone Phone Jack Stereo Connector Solder",Audio-Jack-3_Switch,J3 J4,SJ-3523-SMT-TR,sj-352x-smt,2,http://www.cui.com/product/resource/digikeypdf/sj-352x-smt_s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,Digi-Key,SJ-3523-SMT-TR,load,CP-3523SJCT-ND,CUI Inc.
Fixed Inductors XFL4020 AEC-Q200 2.2 uH 20 % 8 A,L_Small,L1,2.2uH,xfl4020,1,https://www.mouser.com/ds/2/597/xfl4020-270756.pdf,Mouser,XFL4020-222MEB,load,994-XFL4020-222MEB,Coilcraft
FERRITE CHIP 22 OHM 500MA 0603,L_Core_Ferrite,L2,BLM18BA220SN1D,L_0603,1,https://www.murata.com/en-us/products/productdata/8796738650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,Digi-Key,BLM18BA220SN1D,load,490-1016-1-ND,Murata Electronics North America
MOSFET N-CH 60V 190MA TO236AB,Q_NMOS_GSD,Q1 Q2 Q3 Q4 Q5 Q6 Q7 Q8 Q9 Q10 Q11 Q12 Q13 Q14 Q15 Q16 Q17,NX138AKR,SOT-23,17,https://assets.nexperia.com/documents/data-sheet/NX138AK.pdf,Digi-Key,NX138AKR,load,1727-2731-1-ND,Nexperia USA Inc.
RES SMD 100 OHM 0.1% 1/10W 0603,R_Small,R34 R39 R44 R49 R54 R59 R64 R69,100,R_0603,8,https://industrial.panasonic.com/cdbs/www-data/pdf/RDM0000/A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,Digi-Key,ERA-3AEB101V,load,P100DBCT-ND,Panasonic Electronic Components
RES SMD 100K OHM 5% 1/10W 0603,R_Small,R4,100k,R_0603,1,https://industrial.panasonic.com/cdbs/www-data/pdf/RDA0000/A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,Digi-Key,ERJ-3GEYJ104V,load,P100KGCT-ND,Panasonic Electronic Components
RES SMD 107 OHM 1% 1/10W 0603,R_Small,R2,107,R_0603,1,https://industrial.panasonic.com/cdbs/www-data/pdf/RDA0000/A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,Digi-Key,ERJ-3EKF1070V,load,P107HCT-ND,Panasonic Electronic Components
RES 10K OHM 1/10W 5% 0603 SMD,R_Small,R8 R10 R11 R12 R13 R30 R31 R35 R36 R40 R41 R45 R46 R50 R51 R55 R56 R60 R61 R65 R66 R70 R71,10k,R_0603,23,https://industrial.panasonic.com/cdbs/www-data/pdf/RDA0000/A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,Digi-Key,ERJ-3GEYJ103V,load,P10KGCT-ND,Panasonic Electronic Components
RES SMD 220 OHM 5% 1/10W 0603,R_Small,R3,220,R_0603,1,https://industrial.panasonic.com/cdbs/www-data/pdf/RDA0000/A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,Digi-Key,ERJ-3GEYJ221V,load,P220GCT-ND,Panasonic Electronic Components
RES SMD 237 OHM 1% 1/10W 0603,R_Small,R26 R27 R28 R29,237,R_0603,4,https://industrial.panasonic.com/cdbs/www-data/pdf/RDA0000/A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,Digi-Key,ERJ-3EKF2370V,load,P237HCT-ND,Panasonic Electronic Components
RES 3.9 OHM 1/10W 1% 0603 SMD,R_Small,R6,3.9,R_0603,1,https://industrial.panasonic.com/cdbs/www-data/pdf/RDN0000/A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,Digi-Key,ERJ-3RQF3R9V,load,P3.9AJCT-ND,Panasonic Electronic Components
RES SMD 330 OHM 5% 1/10W 0603,R_Small,R32 R33 R37 R38 R42 R43 R47 R48 R52 R53 R57 R58 R62 R63 R67 R68,330,R_0603,16,https://industrial.panasonic.com/cdbs/www-data/pdf/RDA0000/A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,Digi-Key,ERJ-3GEYJ331V,load,P330GCT-ND,Panasonic Electronic Components
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
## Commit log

2020-04-23 add legacy beamforming hardware
